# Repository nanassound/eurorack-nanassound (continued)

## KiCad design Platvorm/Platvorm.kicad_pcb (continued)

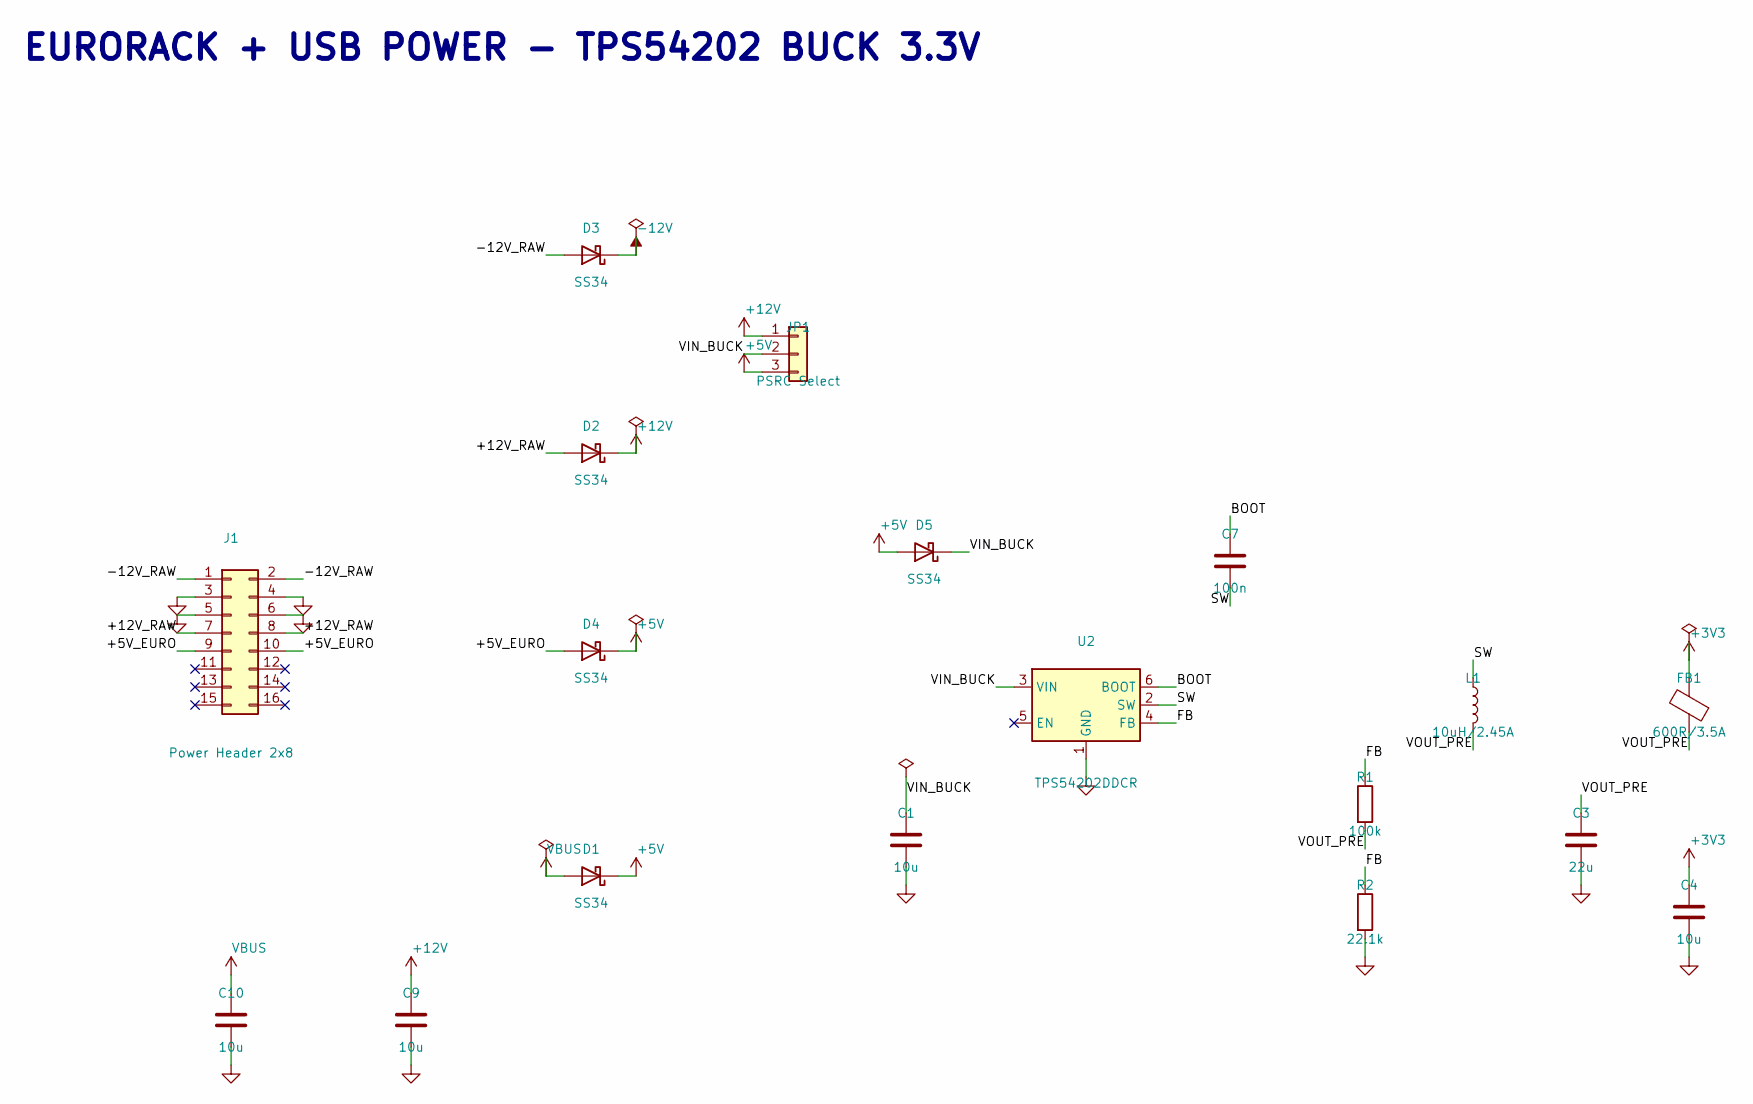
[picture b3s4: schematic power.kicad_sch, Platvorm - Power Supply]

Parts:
C1, C4, C9, C10: 10u; C_0805_2012Metric; MPN CL21A106KAYNNNE; LCSC C15850
C3: 22u; C_0805_2012Metric; MPN CL21A226MAQNNNE; LCSC C45783
C7: 100n; C_0402_1005Metric; MPN CL05B104KO5NNNC; LCSC C1525
D1, D2, D3, D4, D5: SS34; D_SMA; MPN SS34; LCSC C8678
FB1: 600R/3.5A; L_0805_2012Metric; MPN BLM21PG600SN1D; LCSC C18305
J1: Power Header 2x8; PinHeader_2x08_P2.54mm_Vertical; MPN PZ254V-12-16P; LCSC C492425
JP1: PSRC Select; PinHeader_1x03_P2.54mm_Vertical; MPN DZ254R-11-03-63; LCSC C2935909
L1: 10uH/2.45A; IND-SMD_L6.0-W6.0; MPN YNR6045-100M; LCSC C341067
R1: 100k; R_0402_1005Metric; MPN RC0402FR-07100KL; LCSC C25741
R2: 22.1k; R_0402_1005Metric; MPN RC0402FR-0722K1L; LCSC C43473
U2: TPS54202DDCR; SOT-23-6; MPN TPS54202DDCR; LCSC C191884

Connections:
/Power Supply/+5V_EURO: D4.2 (A), J1.9, J1.10
/Power Supply/+12V_RAW: D2.2 (A), J1.7, J1.8
/Power Supply/-12V_RAW: D3.2 (A), J1.1, J1.2
/Power Supply/BOOT: C7.1, U2.6 (BOOT)
/Power Supply/FB: R1.1, R2.1, U2.4 (FB)
/Power Supply/SW: C7.2, L1.1, U2.2 (SW)
/Power Supply/VOUT_PRE: C3.1, FB1.1, L1.2, R1.2
GND: C1.2, C3.2, C4.2, C9.2, C10.2, J1.3, J1.4, J1.5, J1.6, R2.2, U2.1 (GND); also elsewhere on the board

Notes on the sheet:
EURORACK + USB POWER - TPS54202 BUCK 3.3V

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
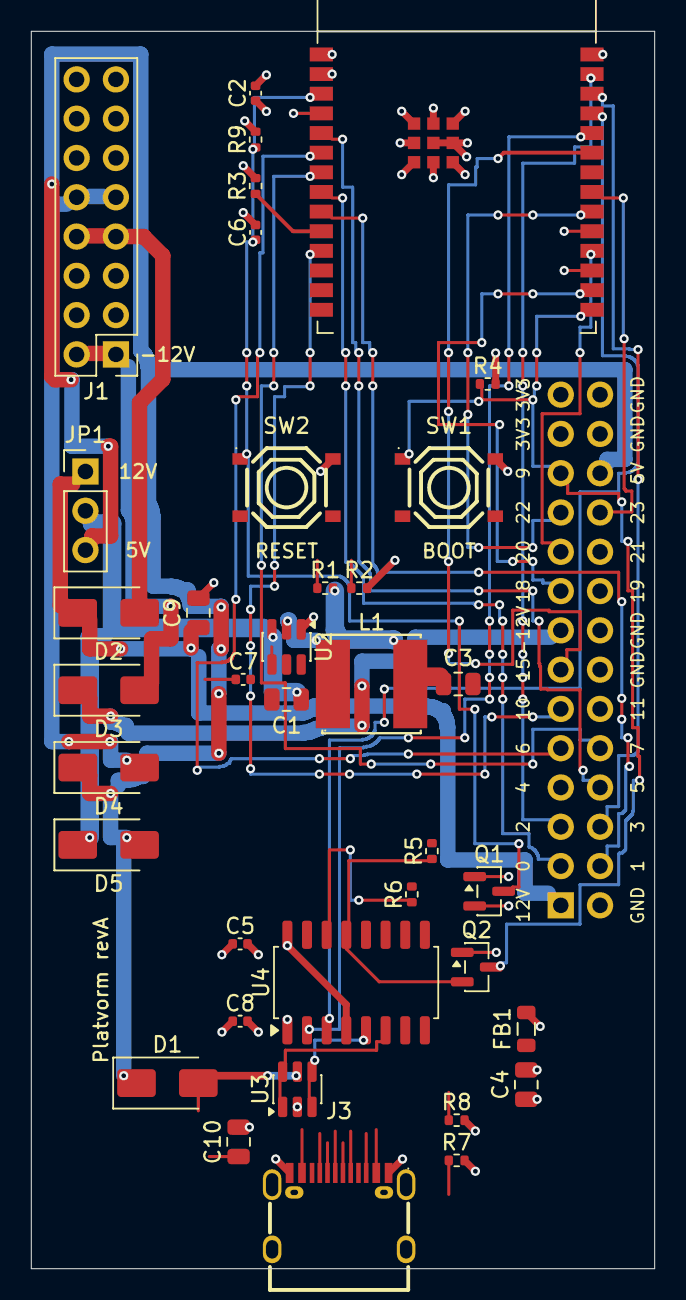
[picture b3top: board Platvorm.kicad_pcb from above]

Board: 4 copper layers, 40.3 x 80.0 mm, 38 parts (1 on the bottom side), 44 nets.

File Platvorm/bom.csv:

"Designator","Comment","Value","Footprint","JLCPCB Part #"
"U1","ESP32-C6-WROOM-1-N8 WiFi6/BLE/802.15.4 module, 8MB flash","ESP32-C6-WROOM-1-N8","platvorm_custom:ESP32-C6-WROOM-1","C5366877"
"U2","TPS54202DDCR buck 4.5-28V 2A 500kHz (3.3V out via R1/R2)","TPS54202DDCR","Package_TO_SOT_SMD:SOT-23-6","C191884"
"U3","USBLC6-2SC6 USB ESD protection","USBLC6-2SC6","Package_TO_SOT_SMD:SOT-23-6","C2687116"
"U4","CH340C USB-UART bridge, internal osc, 3.3V","CH340C","Package_SO:SOP-16_4.4x10.4mm_P1.27mm","C84681"
"FB1","BLM21PG600SN1D ferrite bead 600R@100MHz 3.5A (ripple filter)","600R/3.5A","Inductor_SMD:L_0805_2012Metric","C18305"
"L1","YNR6045-100M 10uH magnetically shielded, Isat 2.45A (replaces unshielded C5289420)","10uH","platvorm_custom:IND-SMD_L6.0-W6.0","C341067"
"D1","SS34: USB VBUS -> +5V rail","SS34","Diode_SMD:D_SMA","C8678"
"D2","SS34: eurorack +12V series protection","SS34","Diode_SMD:D_SMA","C8678"
"D3","SS34: eurorack -12V series protection (reversed)","SS34","Diode_SMD:D_SMA","C8678"
"D4","SS34: eurorack +5V -> +5V rail","SS34","Diode_SMD:D_SMA","C8678"
"D5","SS34: +5V -> VIN_BUCK (USB-only power backup when JP1=12V)","SS34","Diode_SMD:D_SMA","C8678"
"Q1","S8050 NPN: DTR/RTS -> EN auto-reset","S8050","Package_TO_SOT_SMD:SOT-23","C2146"
"Q2","S8050 NPN: DTR/RTS -> IO9 auto-boot","S8050","Package_TO_SOT_SMD:SOT-23","C2146"
"R1","FB divider high (Vout = 0.6*(1+100k/22.1k) = 3.31V)","100k","Resistor_SMD:R_0402_1005Metric","C25741"
"R2","FB divider low","22.1k","Resistor_SMD:R_0402_1005Metric","C43473"
"R3","IO8 strap pull-up","10k","Resistor_SMD:R_0402_1005Metric","C25744"
"R4","IO9/BOOT pull-up","10k","Resistor_SMD:R_0402_1005Metric","C25744"
"R5","Q1 base (DTR), ESP-Prog topology","10k","Resistor_SMD:R_0402_1005Metric","C25744"
"R6","Q2 base (RTS), ESP-Prog topology","10k","Resistor_SMD:R_0402_1005Metric","C25744"
"R7","USB CC1 pull-down 5.1k","5.1k","Resistor_SMD:R_0402_1005Metric","C25905"
"R8","USB CC2 pull-down 5.1k","5.1k","Resistor_SMD:R_0402_1005Metric","C25905"
"R9","EN pull-up","10k","Resistor_SMD:R_0402_1005Metric","C25744"
"C1","Buck input cap 25V X5R","10u","Capacitor_SMD:C_0805_2012Metric","C15850"
"C3","Buck output cap 25V X5R","22u","Capacitor_SMD:C_0805_2012Metric","C45783"
"C4","+3V3 bulk after ferrite bead","10u","Capacitor_SMD:C_0805_2012Metric","C15850"
"C9","+12V rail bulk 25V X5R","10u","Capacitor_SMD:C_0805_2012Metric","C15850"
"C10","VBUS bulk 25V X5R","10u","Capacitor_SMD:C_0805_2012Metric","C15850"
"C2","U1 decoupling","100n","Capacitor_SMD:C_0402_1005Metric","C1525"
"C5","U4 CH340C VCC decoupling","100n","Capacitor_SMD:C_0402_1005Metric","C1525"
"C7","U2 TPS54202 BOOT cap","100n","Capacitor_SMD:C_0402_1005Metric","C1525"
"C8","U4 CH340C V3 decoupling (V3 tied to VCC, 3.3V op)","100n","Capacitor_SMD:C_0402_1005Metric","C1525"
"C6","EN reset delay","1u","Capacitor_SMD:C_0402_1005Metric","C52923"
"SW1","BOOT button (IO9)","TS-1187A","platvorm_custom:SW_TS-1187A","C318884"
"SW2","RESET button (EN)","TS-1187A","platvorm_custom:SW_TS-1187A","C318884"
"J1","PZ254V-12-16P eurorack power 2x8 (pin1=-12V, red stripe)","Power 2x8","Connector_PinHeader_2.54mm:PinHeader_2x08_P2.54mm_Vertical","C492425"
"J2","PZ254V-12-28P daughter-board header 2x14 (see design doc)","GPIO 2x14","Connector_PinHeader_2.54mm:PinHeader_2x14_P2.54mm_Vertical","C22465888"
"JP1","DZ254R-11-03-63 buck source jumper: pin1-2=12V, pin2-3=5V","PSRC Select","Connector_PinHeader_2.54mm:PinHeader_1x03_P2.54mm_Vertical","C2935909"
"J3","TYPE-C-31-M-12 USB-C 16P (power + programming)","USB-C","platvorm_custom:USB-C_SMD-TYPE-C-31-M-12_1","C165948"

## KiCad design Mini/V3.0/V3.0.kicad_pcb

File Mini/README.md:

# Mini: USB-C Power Supply

A small and portable USB-C power supply for Eurorack modules.

- It takes 5V input from USB-C port and outputs dual supply +/- 12V and 5V.
- The main component that converts the voltage is [Mean Well DKM10E-12](https://www.meanwell-web.com/en-gb/dc-dc-converter-pcb-mount-input-4-7-9vdc-dual-dkm10e--12).
- The output current according to DKM10E-12 datasheet is ±0 ~ 416mA.
- The input voltage range is 4.7V ~ 9V.

## Design decisions and changes log

#### Version 3

- Make the PCB dimension smaller. There's no point to mount it on the rail and wasting hit point.
- Reduce the amount of power header to 2 headers only.
- Add some capacitors to avoid noise.
- Add a switch to on/off the power supply without unplugging the cable.

#### Version 2

- Make the PCB dimension to fit 3U height and 6HP width, so it can be mounted on a 3U rack.
- Replace 10 pin power header with 16 pin power header and pass 5V from USB-C to the module.
- Replace the glass fuse with 4A PPTC (resettable fuse) to protect the circuit from over current.
- Use SMT components as much as possible to make the layout cleaner.

#### Version 1

- To allow Mini to use 10 pin power header and keep the design small, it **does not** pass 5V. If the Eurorack module requires 5V, then it's the responsibility of the module to provide it by converting the voltage.
- I add 4A fuse as a safety measure.

## Tested USB-C sources

- MacBook Pro [70W USB-C power adapter](https://www.apple.com/shop/product/MXN53AM/A)
- MacBook Pro M2 USB-C port.
- 40W USB-C phone charger (I don't know the brand)
- Xiaomi 10000mAh USB-A to USB-C power bank

## Tested Eurorack modules

- Nanas Sound Uksed
- Doepfer A-111-6
- Crea8audio Function Junction

## Where to buy Mini?

If you are in Europe, you can buy the fully assembled Mini 2.0 from my store on [Reverb](https://reverb.com/en-ee/item/92160894-nanas-sound-mini-usb-c-power-supply).

For the customer outside of Europe, you can buy it from a shared project on [PCBWay](https://www.pcbway.com/project/shareproject/Mini_Eurorack_modular_synth_USB_C_power_supply_29aeece2.html) or [Elecrow](https://www.elecrow.com/sharepj/mini-eurorack-modular-synth-usb-c-power-supply-988.html).

## Photos from the test of Mini version 1

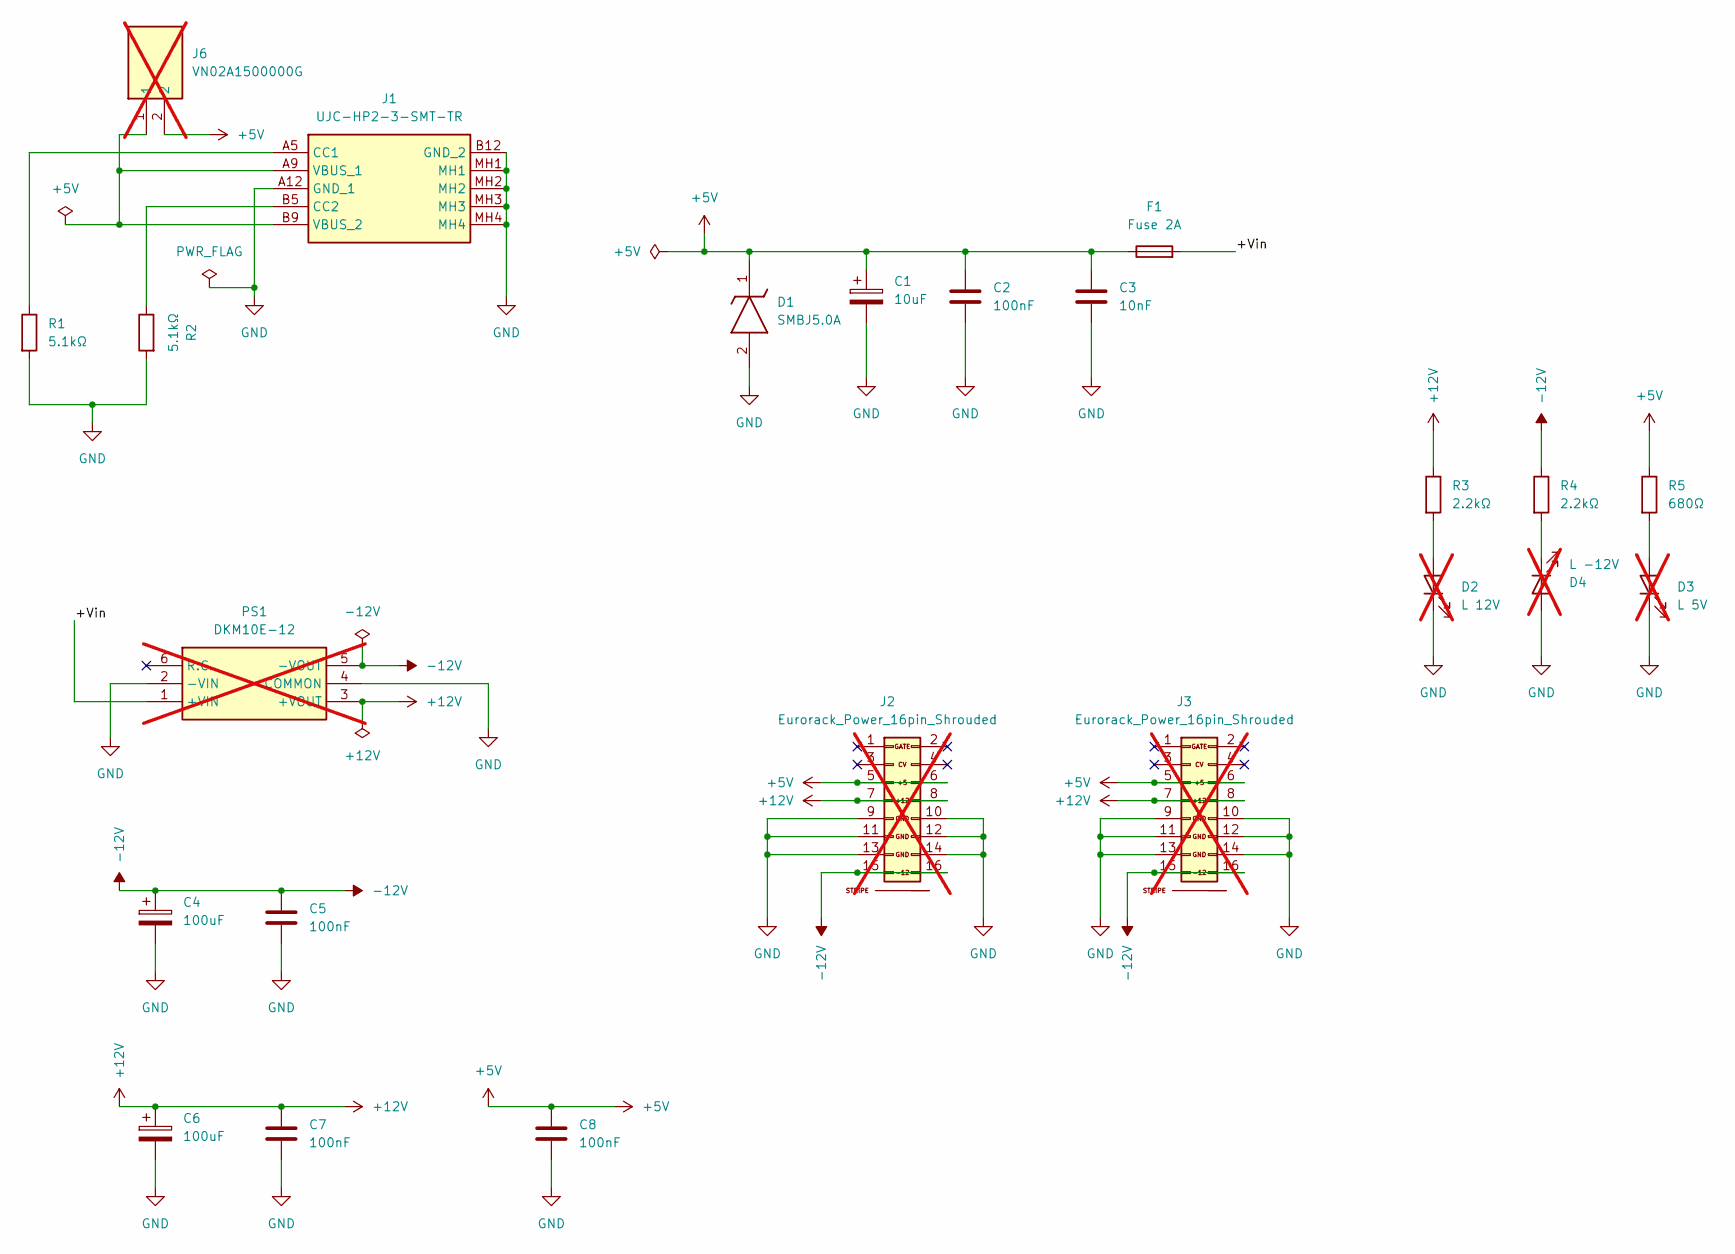
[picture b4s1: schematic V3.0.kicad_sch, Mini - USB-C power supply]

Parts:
C1: 10uF; CP_Elec_6.3x7.7; LCSC Part Number C72482
C2, C5, C7, C8: 100nF; C_0603_1608Metric; LCSC Part Number C14663
C3: 10nF; C_0603_1608Metric; LCSC Part Number C100042
C4, C6: 100uF; CP_Elec_6.3x7.7; LCSC Part Number C48587228
D1: SMBJ5.0A; DIOM5436X244N; Mouser Part Number 652-SMBJ5.0A
D2: L 12V; LED_D2.0mm_W4.8mm_H2.5mm_FlatTop; LCSC Part Number C6717903; not fitted
D3: L 5V; LED_D2.0mm_W4.8mm_H2.5mm_FlatTop; LCSC Part Number C6717903; not fitted
D4: L -12V; LED_D2.0mm_W4.8mm_H2.5mm_FlatTop; LCSC Part Number C6717903; not fitted
F1: Fuse 2A; Fuse_1812_4532Metric; LCSC Part Number C135364
J1: UJC-HP2-3-SMT-TR; UJCHP23SMTTR; Mouser Part Number 179-UJC-HP2-3-SMT-TR
J2, J3: Eurorack_Power_16pin_Shrouded; Pins_2x08_2.54mm_TH_EuroPower_Shrouded_reducedsilk; Part Number LL1007-1 (2*8 HITEMP); not fitted
J6: VN02A1500000G; Mouser Part Number 649-VN02A15000J0G; not fitted
PS1: DKM10E-12; DKM10E12; Mouser Part Number 709-DKM10E-12; not fitted
R1, R2: 5.1kΩ; R_1206_3216Metric; LCSC Part Number C26033
R3, R4: 2.2kΩ; R_1206_3216Metric; LCSC Part Number C17948
R5: 680Ω; R_1206_3216Metric; LCSC Part Number C17975

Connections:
+5V: C1.1, C2.1, C3.1, C8.1, D1.1 (K), F1.1, J2.5 (+12V), J2.6, J3.5 (+12V), J3.6, J6.2, R5.1
+12V: C6.1, C7.1, J2.7 (12V), J2.8 (+12V), J3.7 (12V), J3.8 (+12V), PS1.3 (+VOUT), R3.1
-12V: C4.1, C5.1, J2.15 (-12V), J2.16, J3.15 (-12V), J3.16, PS1.5 (-VOUT), R4.1
/+Vin: F1.2, PS1.1 (+VIN)
GND: C1.2, C2.2, C3.2, C4.2, C5.2, C6.2, C7.2, C8.2, D1.2 (A), D2.1 (K), D3.1 (K), D4.2 (A), J1.A12 (GND_1), J1.B12 (GND_2), J1.MH1, J1.MH2, J1.MH3, J1.MH4, J2.9 (GND), J2.10 (GND), J2.11 (GND), J2.12 (GND), J2.13 (-12), J2.14 (-12V), J3.9 (GND), J3.10 (GND), J3.11 (GND), J3.12 (GND), J3.13 (-12), J3.14 (-12V), PS1.2 (-VIN), PS1.4 (COMMON), R1.2, R2.2
unnamed: D2.2 (A), R3.2
unnamed: D3.2 (A), R5.2
unnamed: D4.1 (K), R4.2
unnamed: J1.A5 (CC1), R1.1
unnamed: J1.B5 (CC2), R2.1
unnamed: J1.A9 (VBUS_1), J1.B9 (VBUS_2), J6.1

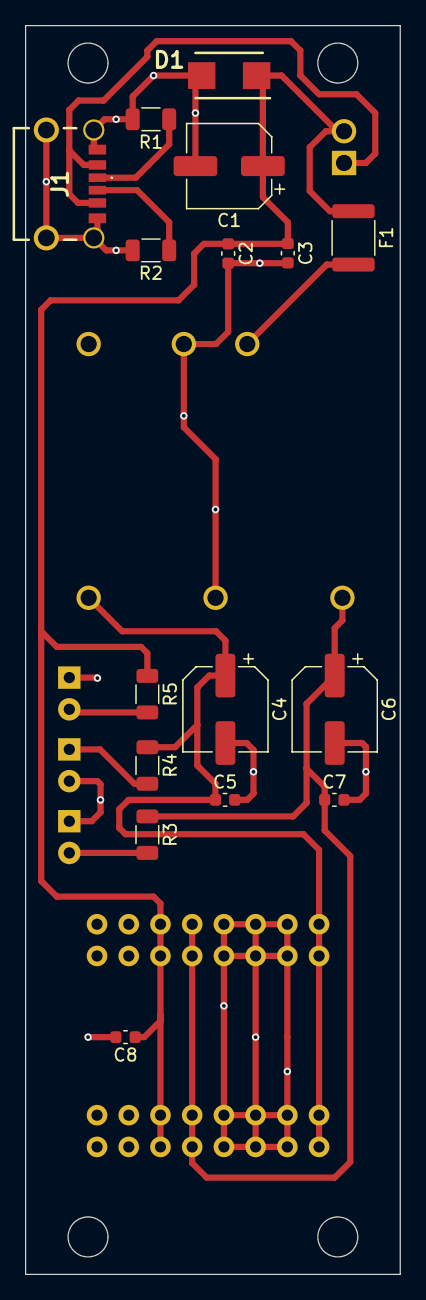
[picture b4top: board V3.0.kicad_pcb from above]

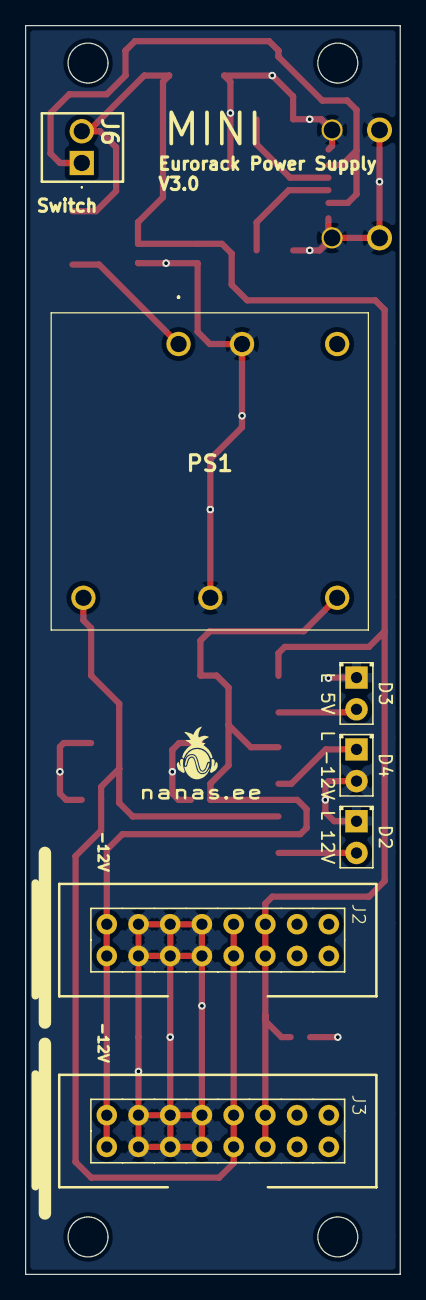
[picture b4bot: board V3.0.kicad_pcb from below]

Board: 2 copper layers, 30.0 x 100.0 mm, 23 parts (7 on the bottom side), 11 nets.

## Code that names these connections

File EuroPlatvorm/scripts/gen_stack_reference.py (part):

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Frames
------
Platform KiCad frame (front view):  x right, y down.
J3 at (137.22, 71.5) LEFT  (power + GPIO0-7 + USB), pins 1..14 running DOWN.
J4 at (149.9,  71.5) RIGHT (GPIO23..8),               pins 1..14 running DOWN.
Headers are THT on the platform BACK (B.Cu) -> a daughter board stacks
back-to-back.  The daughter's KiCad front view equals the platform seen
from behind, i.e. mirrored about the vertical axis, y preserved:
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
# ---------------------------------------------------------------- ground truth
# Platform J3/J4 pinout, taken from the PCB pad net assignments.
J3_NETS = ["+3V3", "+12V", "-12V", "GPIO0", "GPIO1", "GPIO2", "GPIO3",
           "GPIO4", "GPIO5", "GPIO6", "GPIO7", "USB_DP", "USB_DM", "GND"]
J4_NETS = ["GPIO23", "GPIO22", "GPIO21", "GPIO20", "GPIO19", "GPIO18",
           "GPIO17", "GPIO16", "GPIO15", "GPIO11", "GPIO10", "GPIO9",
           "GPIO8", "GND"]

J3_POS = (137.22, 71.5)   # footprint origin, 180 deg, B.Cu
J4_POS = (149.9, 71.5)
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             '\t(layer "F.Cu")\n'
             '\t(descr "EuroPlatvorm carrier stack reference for I/O daughter boards. '
             'Mating field for the two platform back-side 1x14 2.54mm headers: right bank = platform J3 '
             '(+3V3, +12V, -12V, GPIO0-7, USB_DP/DM, GND), left bank = platform J4 (GPIO23-8, GND). '
             'Row spacing 12.68mm (matches platform exactly). Platform outline (21.7x89.75mm) shown on '
             'Dwgs.User; stack back-to-back, daughter B.Cu facing platform B.Cu.")\n'
             '\t(tags "eurorack platvorm europlatvorm carrier daughter shield stack reference esp32-c6")\n')
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    o.append(prop("Datasheet", "", 0, 0, hide=True))
    o.append(prop("Description",
                  "EuroPlatvorm carrier stack reference (ESP32-C6 eurorack platform). "
                  "Place on I/O daughter boards. Right bank = platform J3: +3V3/+12V/-12V, GPIO0-7, "
                  "USB_DP/USB_DM (native USB), GND. Left bank = platform J4: GPIO23..GPIO8, GND. "
                  "GPIO8/GPIO9 are boot strapping pins. Mates with 2x 1x14 2.54mm sockets, "
                  "12.68mm row spacing, platform back-to-back behind the daughter board.", 0, 0, hide=True))
    o.append(prop("ki_keywords", "eurorack platvorm europlatvorm carrier daughter shield esp32-c6", 0, 0, hide=True))
    o.append(prop("ki_fp_filters", "platvorm_custom:EuroPlatvorm*", 0, 0, hide=True))
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
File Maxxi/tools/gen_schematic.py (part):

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
# --- input stage
add('J1', 'Maxxi:USB_C_Receptacle_USB2.0_16P', 'USB_C_Receptacle_USB2.0_16P', FP_USBC, 40, 50,
    pins={'A1B12': ('gnd',), 'B1A12': ('gnd',), 'A4B9': ('net', 'VBUS_RAW'),
          'B4A9': ('net', 'VBUS_RAW'), 'A5': ('net', 'CC1'), 'B5': ('net', 'CC2'),
          'A6': ('nc',), 'B6': ('nc',), 'A7': ('nc',), 'B7': ('nc',),
          'A8': ('nc',), 'B8': ('nc',), '1': ('gnd',), '2': ('gnd',),
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    src=('C55591234', 'LAIL-TYPE-C-16PIN-05-LT', 'LAILAN'), mfr='LAILAN',
    desc='USB Type-C 2.0 receptacle, 16P, SMD vertical (A-row assumed on +Y side of footprint)')
add('F1', 'Device:Polyfuse', '4A/24V', FP_FUSE, 40, 100,
    pins={'1': ('net', 'VBUS_RAW'), '2': ('net', '+VBUS')},
    src=('C42435780', '1812L400/24GR', 'Littelfuse'), mfr='Littelfuse',
    desc='PTC resettable fuse 4A hold 24V (3A hold nuisance-trips at rated loads)')
add('D1', 'Device:D_TVS', 'SMBJ20A', FP_SMB, 62, 105,
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
# --- PD sink
add('U1', 'Maxxi:CH224K', 'CH224K', FP_ESSOP, 130, 55,
    pins={'1': ('net', 'VDD'), '2': ('nc',), '3': ('nc',), '4': ('net', 'DPIO'),
          '5': ('net', 'DPIO'), '6': ('net', 'CC2'), '7': ('net', 'CC1'),
          '8': ('net', 'VBUS_SNS'), '9': ('net', 'CFG1'), '10': ('net', 'PG'),
          '11': ('gnd',)},
    src=('C970725', 'CH224K', 'WCH'), mfr='WCH',
    desc='USB PD sink, CFG1 NC = request 20V; VBUS pin8 via R63 (abs max 13.5V)')
add('R1', 'Device:R', '24k', FP_R, 100, 84, dnp=True, in_bom=False,
    pins={'1': ('net', 'CFG1'), '2': ('gnd',)}, src=R_SRC['24k'], mfr='Yageo',
    desc='CFG1 strap, DNP + excluded from BOM: fit 24k=12V / 56k=15V, NC=20V')
add('R2', 'Device:R', '1k', FP_R1210, 115, 92,
    pins={'1': ('net', '+VBUS'), '2': ('net', 'VDD')},
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    pins={'1': ('net', 'VDD'), '2': ('gnd',)}, src=C_SRC['1uF'], mfr='Samsung',
    desc='CH224K VDD decoupling')
add('R3', 'Device:R', '1k', FP_R, 172, 84,
    pins={'1': ('net', 'DPIO'), '2': ('gnd',)}, src=R_SRC['1k'], mfr='FIRSTART',
    desc='DP/DM pulldown, PD-only mode (datasheet 5.5/6.3)')
add('R4', 'Device:R', '10k', FP_R, 155, 22,
    pins={'1': ('net', 'VDD'), '2': ('net', 'PG')}, src=R_SRC['10k'], mfr='FIRSTART',
    desc='PG open-drain pull-up to VDD (CH224K PG rating unstated; 3.3V-safe)')
add('R63', 'Device:R', '10k', FP_R, 145, 55,
    pins={'1': ('net', '+VBUS'), '2': ('net', 'VBUS_SNS')}, src=R_SRC['10k'], mfr='FIRSTART',
    desc='CH224K VBUS pin8 sense series R (pin abs max 13.5V; WCH v2.1 tab 4-2, fig 7-1: 10k)')

def buck(ref, lref, dref, rbase, cbase, x, y, sfx, pos_net, gnd_net, fb_top, fb_bot, fb_src, diode_lib, diode_val,
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    src=('C459702', 'LT1963AEQ', 'ADI'), mfr='ADI',
    desc='1.5A low-noise LDO, Vout=1.21*(1+90.9/10.2)+3uA*10.2k=12.02V; KiCad symbol: 1=SHDN 2=IN 3=GND 4=OUT 5=ADJ')
add('R50', 'Device:R', '90.9k', FP_R, 252, 62,
    pins={'1': ('net', '+12V'), '2': ('net', 'ADJ1')}, src=R_SRC['90.9k'], mfr='FIRSTART',
    desc='LT1963A ADJ divider top')
add('R51', 'Device:R', '10.2k', FP_R, 266, 62,
    pins={'1': ('net', 'ADJ1'), '2': ('gnd',)}, src=R_SRC['10.2k'], mfr='FIRSTART',
    desc='LT1963A ADJ divider bottom')
add('C50', 'Device:C', '47uF 25V', FP_C1206, 254, 20,
    pins={'1': ('net', '+12V6'), '2': ('gnd',)}, src=C_SRC['47uF 25V'], mfr='Murata',
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    src=('C117305', 'LT3015EDD', 'ADI'), mfr='ADI',
    desc='1.5A negative LDO, Vout=-1.22*(1+R2/R1)=-12.02V (R2=88.7k OUT->ADJ, R1=10k ADJ->GND, LT3015 p15 Fig2/Table1)')
add('R52', 'Device:R', '88.7k', FP_R, 252, 142,
    pins={'1': ('net', '-12V'), '2': ('net', 'ADJ2')}, src=R_SRC['88.7k'], mfr='FIRSTART',
    desc='LT3015 ADJ divider top (OUT->ADJ; p15 Table1: R2 large)')
add('R53', 'Device:R', '10k', FP_R, 266, 142,
    pins={'1': ('net', 'ADJ2'), '2': ('gnd',)}, src=R_SRC['10k'], mfr='FIRSTART',
    desc='LT3015 ADJ divider bottom (ADJ->GND; p15 Table1: R1 small)')
add('C53', 'Device:C', '47uF 25V', FP_C1206, 254, 108,
    pins={'1': ('net', '-12V6'), '2': ('gnd',)}, src=C_SRC['47uF 25V'], mfr='Murata',
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
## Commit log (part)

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2024-09-07 Publishing the schematic
2024-09-07 Fixing the link
2024-09-07 Changing the readme
2024-09-08 Adding oscilloscope reading
2024-09-09 Adding online store link
2024-09-12 Add pico-extras as a submodule
2024-09-13 Setup I2C display and I2S DAC
2024-09-17 Make I2S works.
2024-09-18 Integrating Faust with Pico C++
2024-09-30 Setup FreeRTOS
2024-09-30 Add Mini 2.0
2024-09-30 Adding 5V Mini information
2024-09-30 Change the order of the information
2024-10-15 Change the photo
2024-10-19 Add basic things for the lcd menu.
2024-10-20 Handle the rotary encoder event.
2024-11-01 Adding Mini v2 photos
2025-05-12 Add pick and place file for Mini
2025-08-29 Add Uksed to the repository
2025-08-29 Add shop link for Mini.
2026-04-19 Add Mini V3.0 KiCad project and fix .gitignore for KiCad
    Add schematic, PCB layout, fabrication Gerbers, drill files, pick-and-place
    files, and testing guide for Mini V3.0. Update .gitignore to exclude KiCad
    caches, backup directories, autosave files, lock files, and editor history.
2026-04-19 Adding PDF schematic
2026-04-19 Add Mini V3.0 KiCad project and fix .gitignore for KiCad (#1)
    * Add Mini V3.0 KiCad project and fix .gitignore for KiCad
    Add schematic, PCB layout, fabrication Gerbers, drill files, pick-and-place
    files, and testing guide for Mini V3.0. Update .gitignore to exclude KiCad
    caches, backup directories, autosave files, lock files, and editor history.
    * Adding PDF schematic
2026-04-19 Change readme
